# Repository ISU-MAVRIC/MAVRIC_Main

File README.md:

MAVRIC Main Controller
===========

Hardware and firmware for MAVRIC's main control system

Hardware design files use the [Aerodyne Labs KiCad library](https://github.com/aerodynelabs/kicadlib)

Based off the [ChipKit MAX32](http://www.digilentinc.com/Products/Detail.cfm?NavPath=2,892,894&Prod=CHIPKIT-MAX32)

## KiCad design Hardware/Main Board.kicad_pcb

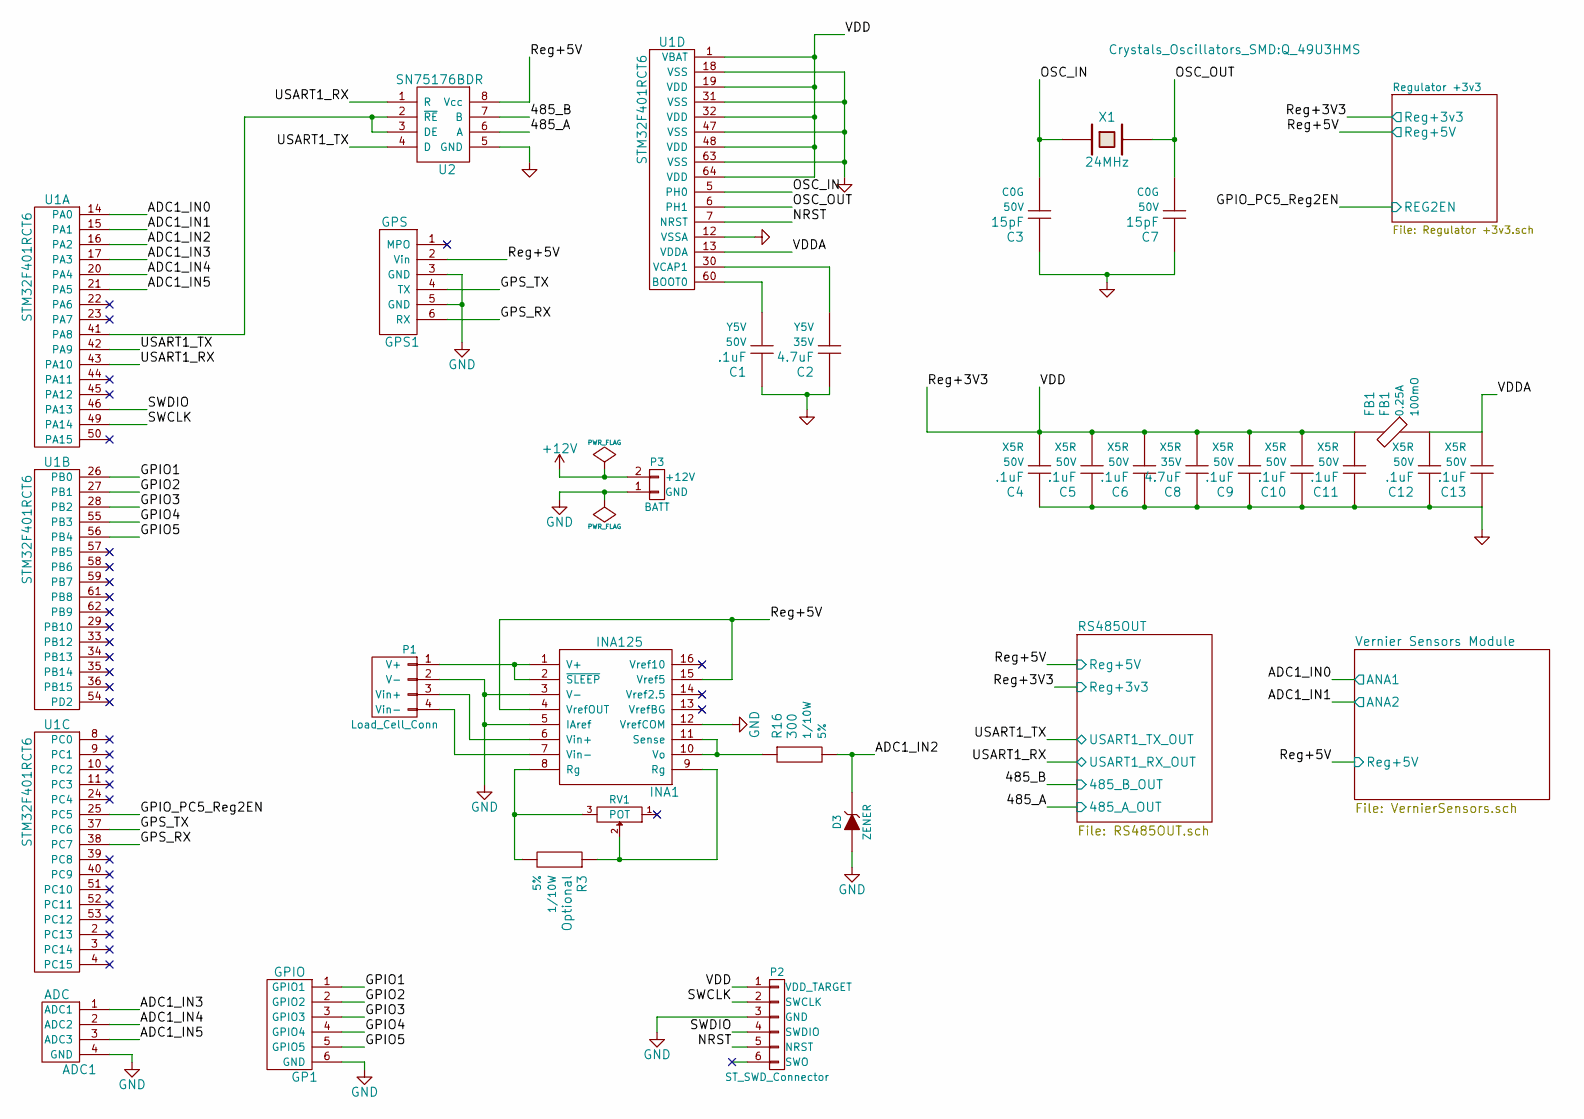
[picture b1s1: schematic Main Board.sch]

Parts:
ADC1: ADC; 1x4_SMD_header
C1, C4, C5, C6, C9, C10, C11, C12, C13: .1uF; C_1206_HandSoldering; Voltage 50V; Manufacturer Part # Value
C2, C8: 4.7uF; C_1206_HandSoldering; Voltage 35V; Manufacturer Part # Value
C3, C7: 15pF; C_1206_HandSoldering; Voltage 50V; Manufacturer Part # Value
D3: ZENER; Diode-SMA_Handsoldering
FB1: FB1; R_1206_HandSoldering; Manufacturer Part # Value
GP1: GPIO; 1x6_SMD_header
GPS1: GPS; GPS_Pads
INA1: INA125; SOIC-16_3.9x9.9mm_Pitch1.27mm
P1: Load_Cell_Conn; 1x4_SMD_header
P2: ST_SWD_Connector; 1x6_Breakaway_Header
P3: BATT; SolderWirePad_2x_2-5mmDrill
R3: Optional; R_1206_HandSoldering; Tolerance 5%; Manufacturer Part # Value
R16: 300; R_1206_HandSoldering; Tolerance 5%; Manufacturer Part # Value
RV1: POT; Potentiometer_Bourns_3006P_Angular_ScrewFront
U1: STM32F401RCT6; LQFP-64_10x10mm_Pitch0.5mm
U2: SN75176BDR; SOIC-8_3.9x4.9mm_Pitch1.27mm
X1: 24MHz; Q_49U3HMS

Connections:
+12V: P3.2 (+12V); also elsewhere on the board
/ADC1_IN2: D3.2 (K), R16.2, U1.16 (PA2)
/ADC1_IN3: ADC1.1 (ADC1), U1.17 (PA3)
/ADC1_IN4: ADC1.2 (ADC2), U1.20 (PA4)
/ADC1_IN5: ADC1.3 (ADC3), U1.21 (PA5)
/GPIO1: GP1.1 (GPIO1), U1.26 (PB0)
/GPIO2: GP1.2 (GPIO2), U1.27 (PB1)
/GPIO3: GP1.3 (GPIO3), U1.28 (PB2)
/GPIO4: GP1.4 (GPIO4), U1.55 (PB3)
/GPIO5: GP1.5 (GPIO5), U1.56 (PB4)
/GPS_RX: GPS1.6 (RX), U1.38 (PC7)
/GPS_TX: GPS1.4 (TX), U1.37 (PC6)
/NRST: P2.5 (NRST), U1.7 (NRST)
/OSC_IN: C3.2, U1.5 (PH0), X1.1
/OSC_OUT: C7.2, U1.6 (PH1), X1.2
/RS485OUT/485_A_OUT: U2.6 (A); also elsewhere on the board
/RS485OUT/485_B_OUT: U2.7 (B); also elsewhere on the board
/RS485OUT/Reg+3V3: C4.2, C5.2, C6.2, C8.2, C9.2, C10.2, C11.2, FB1.1, P2.1 (VDD_TARGET), U1.1 (VBAT), U1.19 (VDD), U1.32 (VDD), U1.48 (VDD), U1.64 (VDD); also elsewhere on the board
/RS485OUT/Reg+5V: GPS1.2 (Vin), INA1.4 (VrefOUT), INA1.15 (Vref5), U2.8 (Vcc); also elsewhere on the board
/RS485OUT/USART1_RX_OUT: U1.43 (PA10), U2.1 (R); also elsewhere on the board
/RS485OUT/USART1_TX_OUT: U1.42 (PA9), U2.4 (D); also elsewhere on the board
/Regulator +3v3/REG2EN: U1.25 (PC5); also elsewhere on the board
/SWCLK: P2.2 (SWCLK), U1.49 (PA14)
/SWDIO: P2.4 (SWDIO), U1.46 (PA13)
/VDDA: C12.2, C13.2, FB1.2, U1.13 (VDDA)
/Vernier Sensors Module/ANA1: U1.14 (PA0); also elsewhere on the board
/Vernier Sensors Module/ANA2: U1.15 (PA1); also elsewhere on the board
GND: ADC1.4 (GND), C1.1, C2.1, C3.1, C4.1, C5.1, C6.1, C7.1, C8.1, C9.1, C10.1, C11.1, C12.1, C13.1, D3.1 (A), GP1.6 (GND), GPS1.3 (GND), GPS1.5 (GND), INA1.3 (V-), INA1.5 (IAref), INA1.12 (VrefCOM), P1.2 (V-), P2.3 (GND), P3.1 (GND), U1.12 (VSSA), U1.18 (VSS), U1.31 (VSS), U1.47 (VSS), U1.63 (VSS), U2.5 (GND); also elsewhere on the board
unnamed: C1.2, U1.60 (BOOT0)
unnamed: C2.2, U1.30 (VCAP1)
unnamed: INA1.1 (V+), INA1.2 (~SLEEP), P1.1 (V+)
unnamed: INA1.6 (Vin+), P1.3 (Vin+)
unnamed: INA1.7 (Vin-), P1.4 (Vin-)
unnamed: INA1.8 (Rg), R3.2, RV1.3
unnamed: INA1.9 (Rg), R3.1, RV1.2
unnamed: INA1.10 (Vo), INA1.11 (Sense), R16.1
unnamed: U1.41 (PA8), U2.2 (~RE), U2.3 (DE)

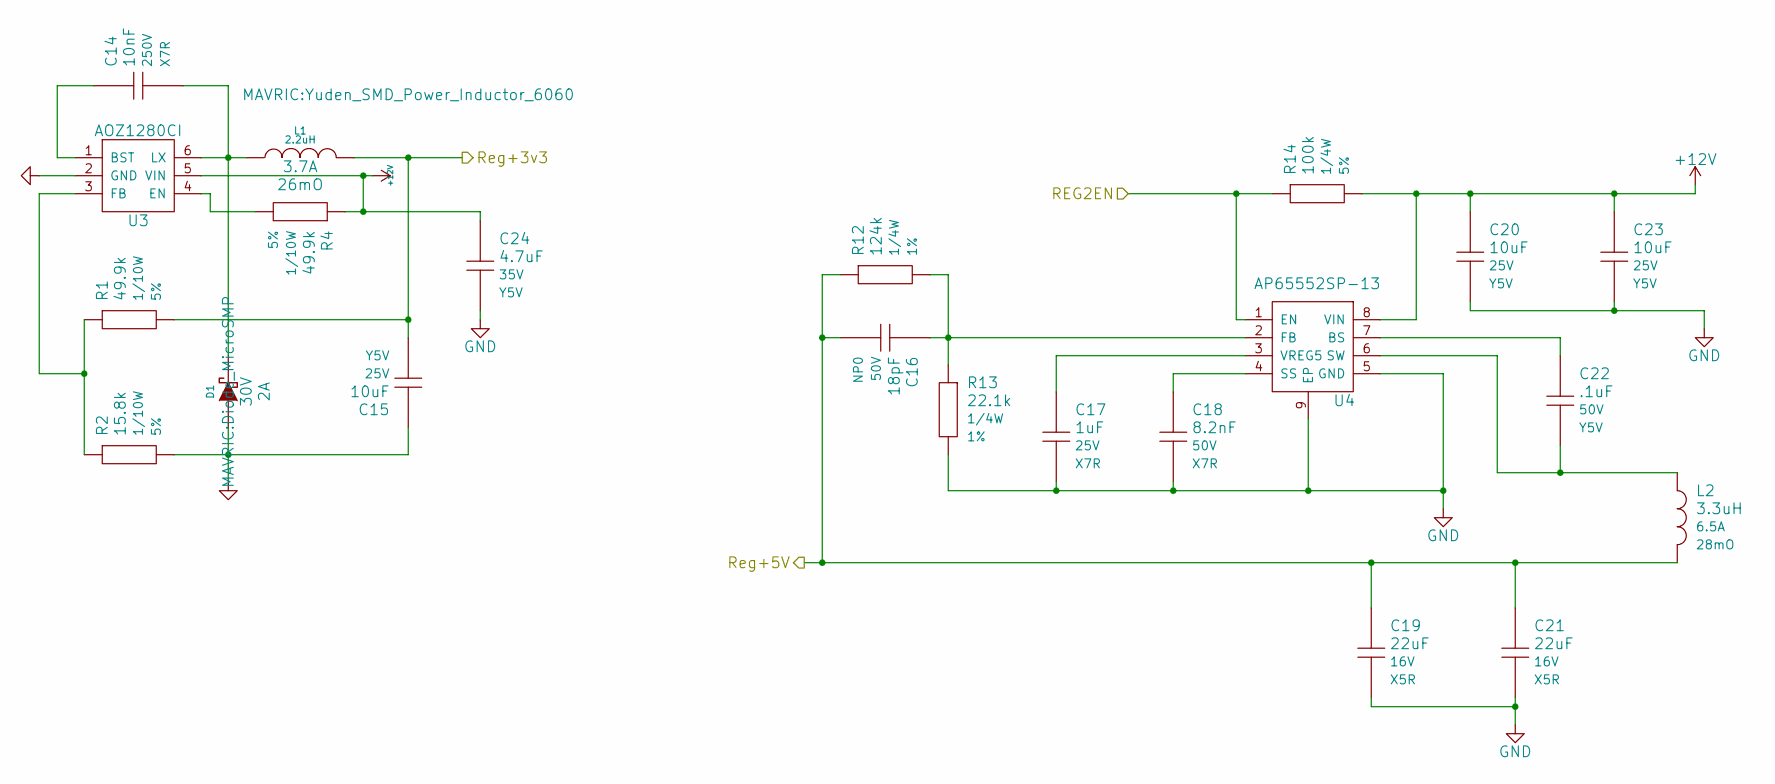
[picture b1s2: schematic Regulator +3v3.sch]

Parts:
C14: 10nF; C_1206_HandSoldering; Voltage 250V; Manufacturer Part # Value
C15, C20, C23: 10uF; C_1206_HandSoldering; Voltage 25V; Manufacturer Part # Value
C16: 18pF; C_1206_HandSoldering; Voltage 50V; Manufacturer Part # Value
C17: 1uF; C_1206_HandSoldering; Voltage 25V; Manufacturer Part # Value
C18: 8.2nF; C_1206_HandSoldering; Voltage 50V; Manufacturer Part # Value
C19, C21: 22uF; C_1206_HandSoldering; Voltage 16V; Manufacturer Part # Value
C22: .1uF; C_1206_HandSoldering; Voltage 50V; Manufacturer Part # Value
C24: 4.7uF; C_1206_HandSoldering; Voltage 35V; Manufacturer Part # Value
D1: DIODESCH; Diode_MicroSMP; Reverse Voltage 30V
L1: 2.2uH; Yuden_SMD_Power_Inductor_6060
L2: 3.3uH; Neosid_Inductor_SM-PIC0612H; Manufacturer Part # Value
R1, R4: 49.9k; R_1206_HandSoldering; Tolerance 5%; Manufacturer Part # Value
R2: 15.8k; R_1206_HandSoldering; Tolerance 5%; Manufacturer Part # Value
R12: 124k; R_1206_HandSoldering; Tolerance 1%; Manufacturer Part # Value
R13: 22.1k; R_1206_HandSoldering; Tolerance 1%; Manufacturer Part # Value
R14: 100k; R_1206_HandSoldering; Tolerance 5%; Manufacturer Part # Value
U3: AOZ1280CI; SOT-23-6
U4: AP65552SP-13; SOIC-8-1EP_3.9x4.9mm_Pitch1.27mm

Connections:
+12V: C20.1, C23.1, C24.1, R4.1, R14.2, U3.5 (VIN), U4.8 (VIN); also elsewhere on the board
/RS485OUT/Reg+3V3: C15.2, L1.2, R1.2; also elsewhere on the board
/RS485OUT/Reg+5V: C16.2, C19.1, C21.1, L2.2, R12.1; also elsewhere on the board
/Regulator +3v3/REG2EN: R14.1, U4.1 (EN); also elsewhere on the board
GND: C15.1, C17.2, C18.2, C19.2, C20.2, C21.2, C23.2, C24.2, D1.1 (A), R2.2, R13.2, U3.2 (GND), U4.5 (GND), U4.9 (EP); also elsewhere on the board
unnamed: C14.1, U3.1 (BST)
unnamed: C14.2, D1.2 (K), L1.1, U3.6 (LX)
unnamed: C16.1, R12.2, R13.1, U4.2 (FB)
unnamed: C17.1, U4.3 (VREG5)
unnamed: C18.1, U4.4 (SS)
unnamed: C22.1, U4.7 (BS)
unnamed: C22.2, L2.1, U4.6 (SW)
unnamed: R1.1, R2.1, U3.3 (FB)
unnamed: R4.2, U3.4 (EN)

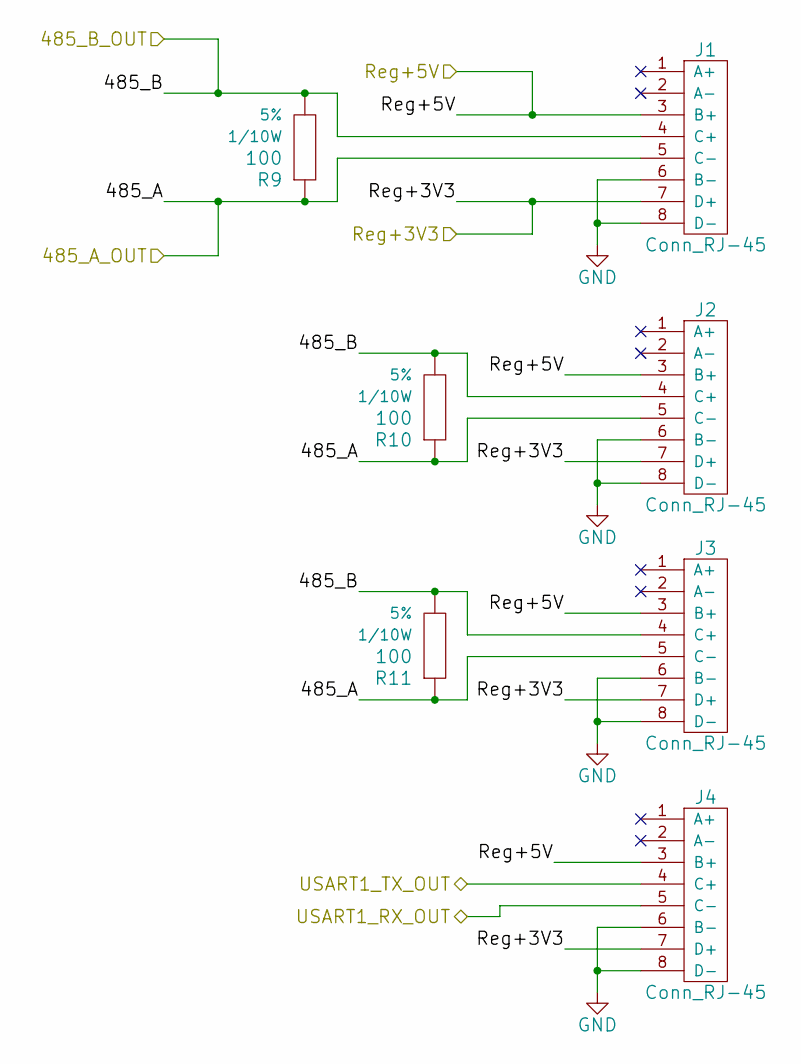
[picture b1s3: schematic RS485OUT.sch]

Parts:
J1, J2, J3, J4: Conn_RJ-45; Molex_RJ45_0437438101
R9, R10, R11: 100; R_1206_HandSoldering; Tolerance 5%; Manufacturer Part # Value

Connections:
/RS485OUT/485_A_OUT: J1.5 (C-), J2.5 (C-), J3.5 (C-), R9.1, R10.1, R11.1; also elsewhere on the board
/RS485OUT/485_B_OUT: J1.4 (C+), J2.4 (C+), J3.4 (C+), R9.2, R10.2, R11.2; also elsewhere on the board
/RS485OUT/Reg+3V3: J1.7 (D+), J2.7 (D+), J3.7 (D+), J4.7 (D+); also elsewhere on the board
/RS485OUT/Reg+5V: J1.3 (B+), J2.3 (B+), J3.3 (B+), J4.3 (B+); also elsewhere on the board
/RS485OUT/USART1_RX_OUT: J4.5 (C-); also elsewhere on the board
/RS485OUT/USART1_TX_OUT: J4.4 (C+); also elsewhere on the board
GND: J1.6 (B-), J1.8 (D-), J2.6 (B-), J2.8 (D-), J3.6 (B-), J3.8 (D-), J4.6 (B-), J4.8 (D-); also elsewhere on the board

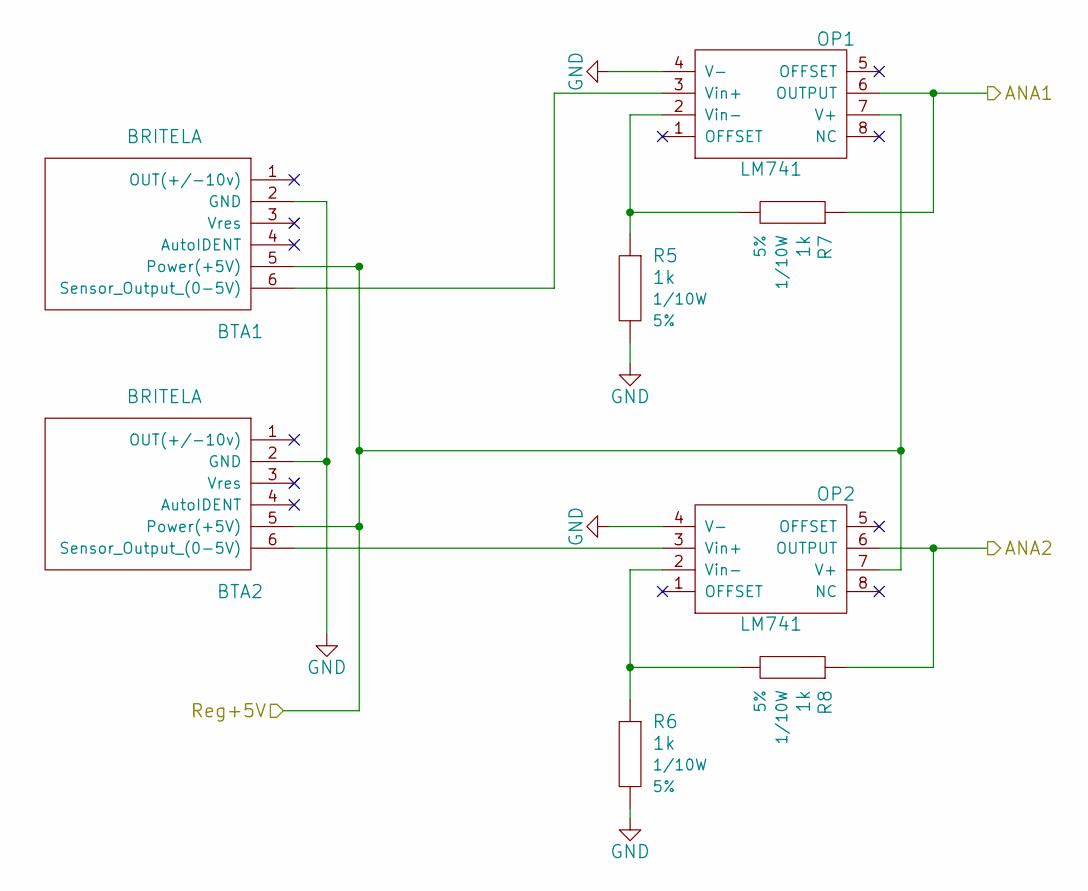
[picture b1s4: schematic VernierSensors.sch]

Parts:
BTA1, BTA2: BRITELA; BTA
OP1, OP2: LM741; SOIC-8_3.9x4.9mm_Pitch1.27mm
R5, R6, R7, R8: 1k; R_1206_HandSoldering; Tolerance 5%; Manufacturer Part # Value

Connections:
/RS485OUT/Reg+5V: BTA1.5 (Power(+5V)), BTA2.5 (Power(+5V)), OP1.7 (V+), OP2.7 (V+); also elsewhere on the board
/Vernier Sensors Module/ANA1: OP1.6 (OUTPUT), R7.1; also elsewhere on the board
/Vernier Sensors Module/ANA2: OP2.6 (OUTPUT), R8.1; also elsewhere on the board
GND: BTA1.2 (GND), BTA2.2 (GND), OP1.4 (V-), OP2.4 (V-), R5.2, R6.2; also elsewhere on the board
unnamed: BTA1.6 (Sensor_Output_(0-5V)), OP1.3 (Vin+)
unnamed: BTA2.6 (Sensor_Output_(0-5V)), OP2.3 (Vin+)
unnamed: OP1.2 (Vin-), R5.1, R7.2
unnamed: OP2.2 (Vin-), R6.1, R8.2

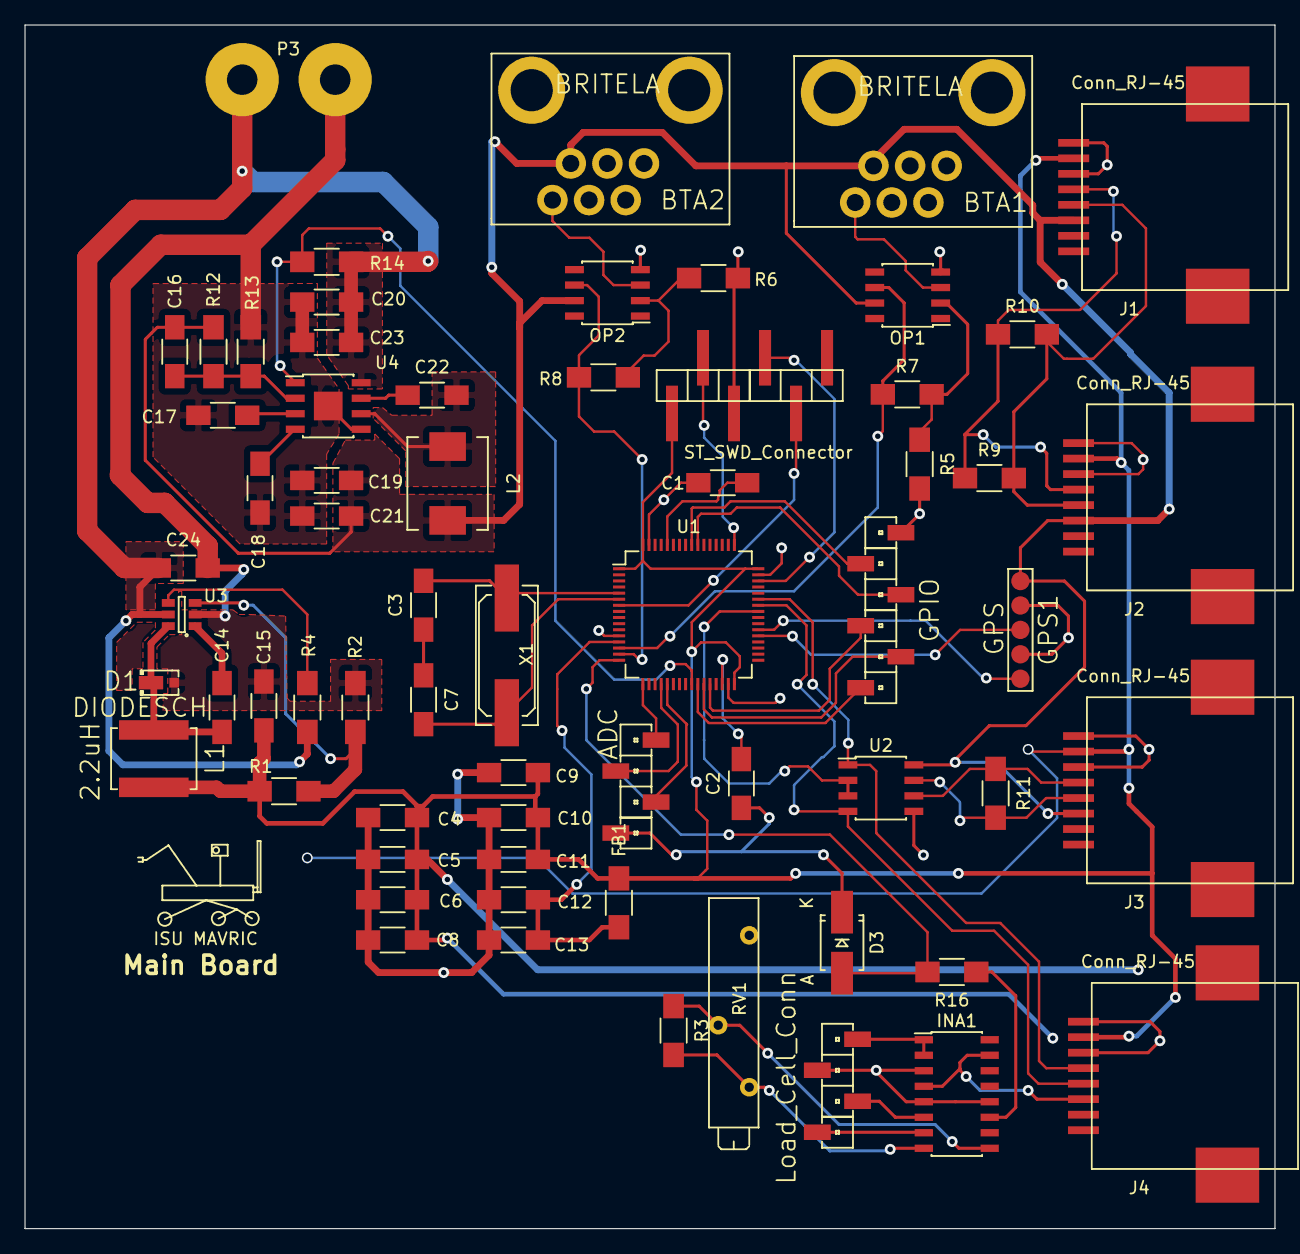
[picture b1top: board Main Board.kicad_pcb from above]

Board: 2 copper layers, 102.4 x 98.6 mm, 66 parts (0 on the bottom side), 50 nets.

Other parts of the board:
ISU MAVRIC: VAL**; MAVRIC_LOGO

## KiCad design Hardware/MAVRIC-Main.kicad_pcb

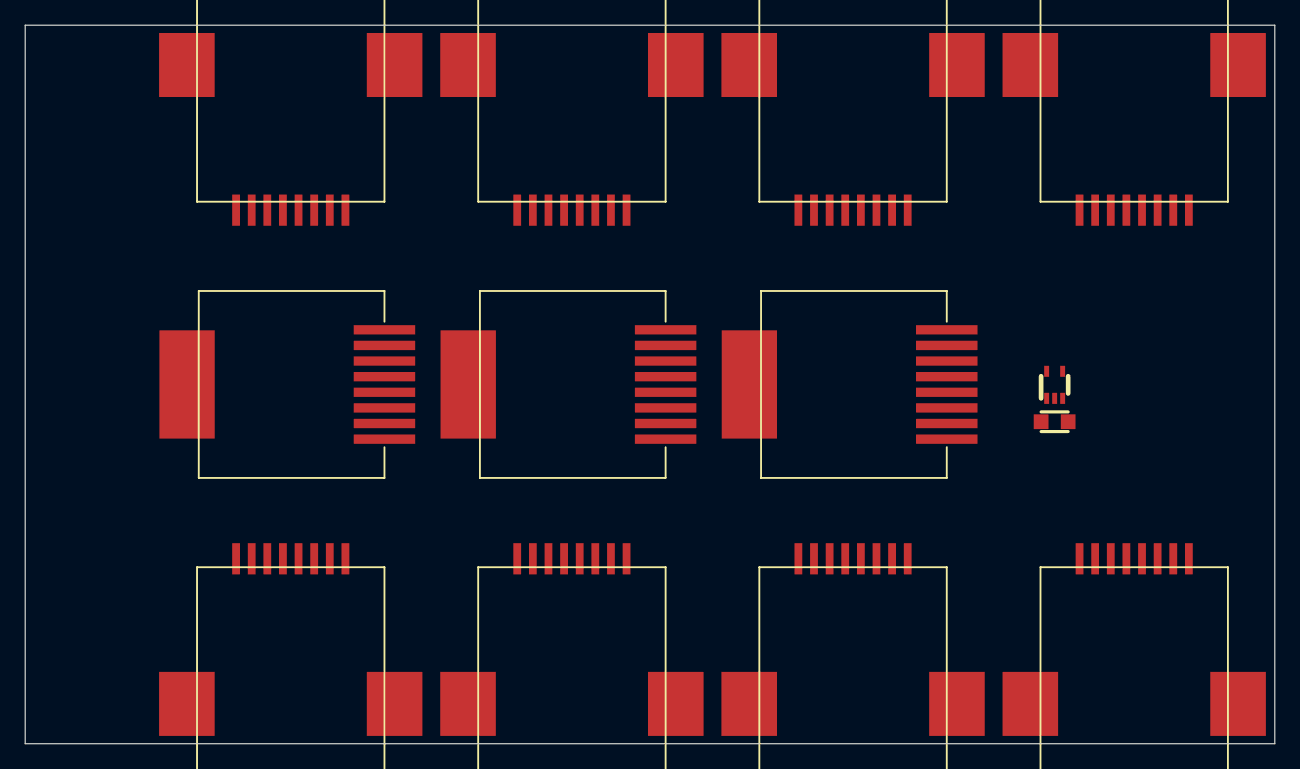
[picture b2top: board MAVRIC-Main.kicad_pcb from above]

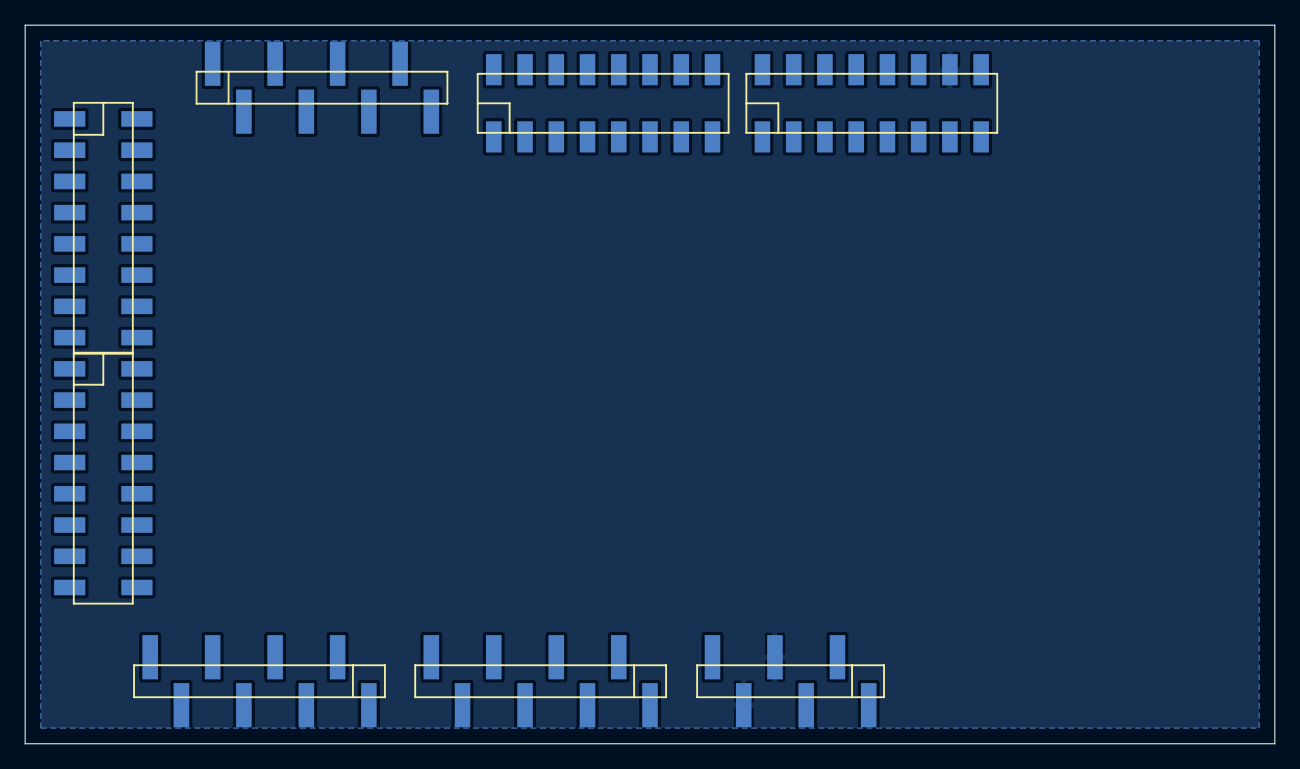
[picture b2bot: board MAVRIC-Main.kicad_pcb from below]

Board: 2 copper layers, 101.6 x 58.4 mm, 21 parts (8 on the bottom side), 42 nets, no tracks yet.

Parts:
C1: 0.1uF; CAPC2012
J1: MTR1; CONN-WM6469CT
J2: MTR4; CONN-WM6469CT
J3: MTR2; CONN-WM6469CT
J4: MTR5; CONN-WM6469CT
J5: MTR3; CONN-WM6469CT
J6: MTR6; CONN-WM6469CT
J7: VID; CONN-WM6469CT
J8: DAT; CONN-WM6469CT
J9: ARM; CONN-WM3553CT
J10: CAM; CONN-WM3553CT
J11: CK-PWR; HDRV6W38P254_6X1-SMT
J12: CK-A0; HDRV8W38P254_8X1-SMT
J13: CK-A1; HDRV8W38P254_8X1-SMT
J14: CK-COM; HDRV8W38P254_8X1-SMT
J15: CK-D0; HDRV16W64P254_8X2-SMT
J16: CK-X0; HDRV16W64P254_8X2-SMT
J17: CK-D1; HDRV16W64P254_8X2-SMT
J18: CK-X1; HDRV16W64P254_8X2-SMT
J19: GPS; CONN-WM3553CT
U1: SN74LVC1G125; SOT65P210X110-5N

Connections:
+3.3V: J1.3, J2.3, J3.3, J4.3, J5.3, J6.3, J11.2
+5V: C1.1, J11.3, J19.4, J19.5, U1.1, U1.5
+BATT: J7.4, J7.5, J8.4, J8.5, J10.4, J10.5, J11.6
/A1: J1.7, J12.2
/A2: J3.7, J12.3
/A3: J5.7, J12.4
/A4: J2.7, J12.5, J17.12
/A5: J4.7, J12.6
/A6: J6.7, J12.7
/CK2: J6.2, J15.6
/CK3: J6.4, J15.8
/CK4: J6.5, J15.10
/CK5: J6.6, J15.12
/CK6: J4.2, J15.14
/CK7: J4.4, J15.16
/CK8: J4.5, J17.2
/CK9: J4.6, J17.4
/CK10: J2.2, J17.6
/CK11: J2.5, J17.8
/CK12: J2.6, J17.10
/CK74: J5.6, J15.9
/CK75: J5.5, J15.11
/CK76: J5.4, J15.13
/CK77: J5.2, J15.15
/CK78: J3.6, J17.1
/CK79: J3.5, J17.3
/CK80: J3.4, J17.5
/CK81: J3.2, J17.7
/CK82: J1.6, J17.9
/CK83: J1.5, J17.11
/CK84: J1.4, J17.13
/CK85: J1.2, J17.15
/MotorTx: J1.1, J2.1, J3.1, J4.1, J5.1, J6.1, U1.4
/RX0: J8.3, J15.2
/RX1: J14.3, J19.1
/RX3: J10.6, J14.7
/TX0: J8.1, J15.4
/TX1: J14.4, U1.2
/TX3: J10.3, J14.8
/VidGnd: J7.2, J10.1
/Video: J7.1, J10.2
GND: C1.2, J1.8, J2.8, J3.8, J4.8, J5.8, J6.8, J7.7, J7.8, J8.2, J8.6, J8.7, J8.8, J10.7, J10.8, J11.4, J11.5, J17.14, J19.2, J19.7, J19.8, U1.3

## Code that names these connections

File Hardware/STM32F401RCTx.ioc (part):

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Mcu.Name=STM32F401R(B-C-D-E)Tx
Mcu.Package=LQFP64
Mcu.UserName=STM32F401RCTx
PA10.Mode=Asynchronous
PA10.Signal=USART1_RX
PA2.Mode=Asynchronous
PA2.Signal=USART2_TX
PA3.Mode=Asynchronous
PA3.Signal=USART2_RX
PA9.Mode=Asynchronous
PA9.Signal=USART1_TX
RCC.HSE_VALUE=25000000
RCC.SYSCLKFreq_VALUE=16000000

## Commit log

2013-09-07 Create KiCad project
2013-09-07 Add basic connector and ChipKit headers
2013-09-07 Replace arm and camera connectors with vertical style
2013-09-08 Add simple firmware
2013-09-08 Reload packages for 3D models and fix typo
    See AerodyneLabs/KiCadLib@c14934719a961a2749f372fa06ca804ae15d519b for
    typo
2013-09-09 Swap vid/agnd to comply with camera change
2013-09-10 Rough pin out of most systems
2013-09-12 Finish 1v0 circuit board!
2013-09-26 Organizing Code
2013-09-27 Main Firmware update
    Created a sketch in MPIDE. Basic command parsing works.
2013-09-28 Add some bom values
2013-10-01 Control motors using packetized serial mode
2013-11-12 Beginning of inter-board communication
    Changed serial buffer to pass entire commands
2014-09-16 Organized Folder, Initial Commit of Basic Control
2014-09-16 Added Feature: Wheels Turn Now
2014-09-16 Serial Control: Forward and Reverse
2014-09-16 Fixed the serial to match wireless speed
2014-10-25 Board now accepts primative motor speed packets
    Board accepts packets in format <+000 -000> form where the first value
    is the left motor speeds and the second value is the right motor speeds.
    The packet is parsed to integers and returned over serial. Value is NOT
    sent to motors yet
2014-10-25 Primitive serial control: Motors now work
2014-10-25 Changed when the newline is sent
    Now the robot moves
2014-11-01 Removed old code and updated intro comments
2014-11-01 Created separate program for arm control
    Duplicated wheel control, made a couple of changes for two motors versus
    six
2014-11-19 Added Pan Tilt Control Code
    Still separate from everything else
2014-11-19 Adds Pan and Tilt control to the camera controller
2014-11-27 Adjusted for non-continuous servos
    Angle addition to allow for angle holding and pan/tilt in the negative
    direction.
2014-12-04 Fixed random motion
    Adjusted the values because servo does not tolerate values less than
    three or more than 180
2014-12-06 Now controls both servos and centers forward
2014-12-13 Nucleo Test Code in CoIDE
    User button toggles LED State, has debouncing issues.
2015-01-11 Basic PWM control and conversion to C++
    She's beautiful ... she's rich ... she's got huge ... tracts of
    commented out code
2015-01-11 Now two PWM pins work
    what a major world accomplishment someone call al jazeera
2015-01-11 Cleaned up unused TIM3 stuff
    just committing a bunch to get a dark green square on my github profile
    for today
2015-01-11 Two PWM with more cleanup
    committing for reference when changing to timer 1 due to ST-Link
    conflict on the serial port
2015-01-11 Changed over to TIM1, added debug support
    TIM1 doesn't work currently but debugging does. It sometimes crashes
    CoIDE but I'm not sure if that's something I can fix
2015-01-12 Changed to TIM4 -
2015-01-16 MAVRIC_Main.zip is the exported mbed project
    You can import it into the online mbed ide. They don't make it easy to
    share code so this will have to do until we export everything to coocox
2015-01-29 Added mbed project. Reogranized some old stuff
2015-01-31 Filled out MAVRIC_Main, fixed minor issues
2015-02-02 Created KiCad project and STMCube project
2015-03-07 Add 5v regulator and RS485 transceiver to Main board
    Added RS485 and a 5v regulator to power it
2015-04-03 Add BTA breakout for Vernier sensors and convert 5v analog to 3v3
2015-04-04 Add 485 network out, POE for Wheel Pod boards
2015-04-18 Add instrumentation amplifier for load cell, added amplifiers for ph and moisture sensors
2015-04-18 Fix capacitor annotation problem
    The capacitors from the same library were assigned the same numbers for
    an unknown reason.
2015-04-24 Fix annotation problem, Add IC datasheets
2015-05-02 Add GPS Pads, potentiometer to INA125, 3v3 regulator always enabled, footprints created for GPS Pads and BTA, parts assigned
2015-05-02 Merge remote-tracking branch 'origin/master'
    Conflicts:
    Hardware/Main Board-cache.lib
    Hardware/Main Board.cmp
    Hardware/Main Board.net
    Hardware/Main Board.pro
    Hardware/Main Board.sch
2015-05-02 Finish Main Board schematic
2015-05-05 PCB Main Board for Mark
2015-05-05 Layout of PCB
2015-05-05 PCB Almost Complete
2015-05-05 Add ground Plane
2015-05-05 Main Board Finished
